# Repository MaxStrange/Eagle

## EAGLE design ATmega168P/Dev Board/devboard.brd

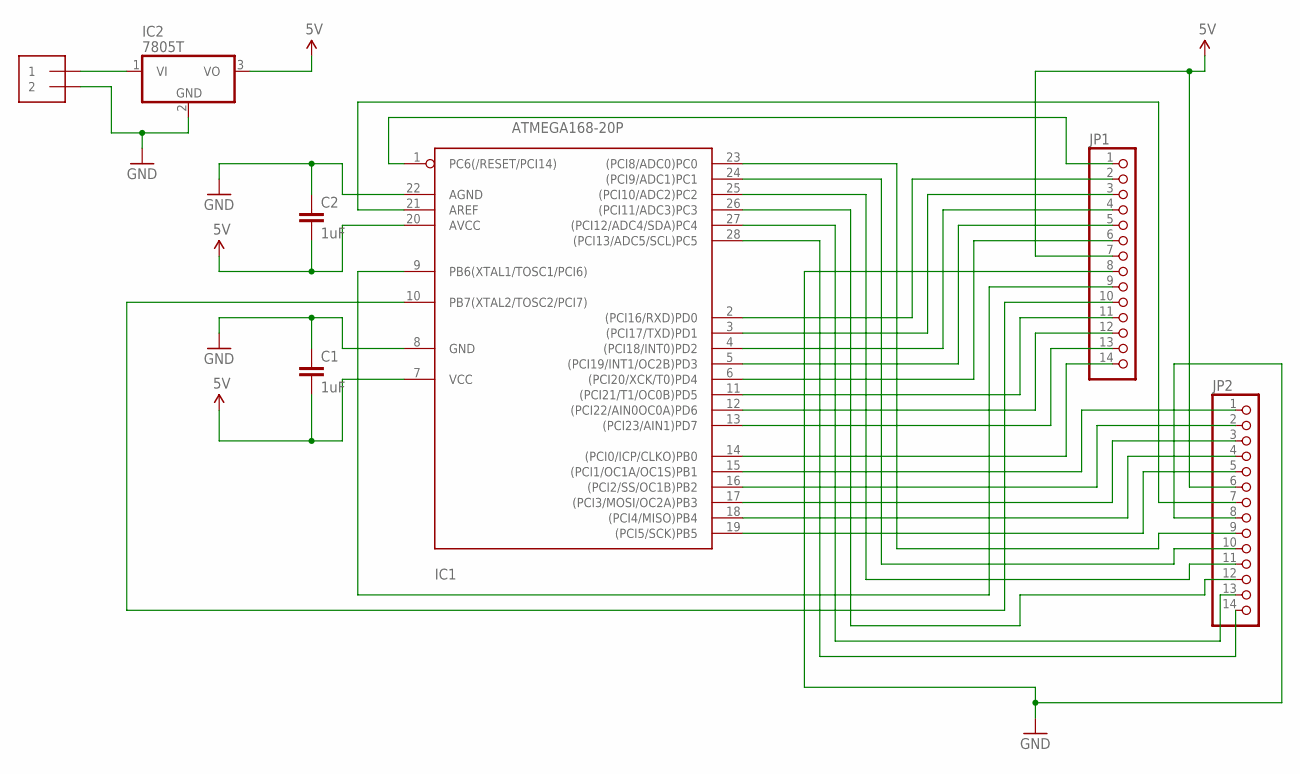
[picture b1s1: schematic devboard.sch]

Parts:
C1, C2: 1uF; CAP-PTH-SMALL
IC1: ATMEGA168-20P; DIL28-3
IC2: 7805T; TO220H
JP1, JP2: PINHD-1X14; 1X14
POWER_IN: 1X2-3.5MM

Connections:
GND: C1.1, C2.1, IC1.8 (GND), IC1.22 (AGND), IC2.2 (GND), JP1.8, JP2.8, POWER_IN.2
MISO: IC1.18 ((PCI4/MISO)PB4), JP2.4
MOSI: IC1.17 ((PCI3/MOSI/OC2A)PB3), JP2.3
unnamed: IC1.1 (PC6(/RESET/PCI14)), JP1.1
PIN2: IC1.2 ((PCI16/RXD)PD0), JP1.2
PIN3: IC1.3 ((PCI17/TXD)PD1), JP1.3
PIN4: IC1.4 ((PCI18/INT0)PD2), JP1.4
PIN5: IC1.5 ((PCI19/INT1/OC2B)PD3), JP1.5
PIN6: IC1.6 ((PCI20/XCK/T0)PD4), JP1.6
PIN9: IC1.9 (PB6(XTAL1/TOSC1/PCI6)), JP1.9
PIN10: IC1.10 (PB7(XTAL2/TOSC2/PCI7)), JP1.10
PIN11: IC1.11 ((PCI21/T1/OC0B)PD5), JP1.11
PIN12: IC1.12 ((PCI22/AIN0OC0A)PD6), JP1.12
PIN13: IC1.13 ((PCI23/AIN1)PD7), JP1.13
PIN14: IC1.14 ((PCI0/ICP/CLKO)PB0), JP1.14
PIN15: IC1.15 ((PCI1/OC1A/OC1S)PB1), JP2.1
PIN16: IC1.16 ((PCI2/SS/OC1B)PB2), JP2.2
PIN21: IC1.21 (AREF), JP2.7
PIN23: IC1.23 ((PCI8/ADC0)PC0), JP2.9
PIN24: IC1.24 ((PCI9/ADC1)PC1), JP2.10
PIN25: IC1.25 ((PCI10/ADC2)PC2), JP2.11
PIN26: IC1.26 ((PCI11/ADC3)PC3), JP2.12
PIN27: IC1.27 ((PCI12/ADC4/SDA)PC4), JP2.13
PIN28: IC1.28 ((PCI13/ADC5/SCL)PC5), JP2.14
SCK: IC1.19 ((PCI5/SCK)PB5), JP2.5
VCC: C1.2, C2.2, IC1.7 (VCC), IC1.20 (AVCC), IC2.3 (VO), JP1.7, JP2.6
VIN: IC2.1 (VI), POWER_IN.1

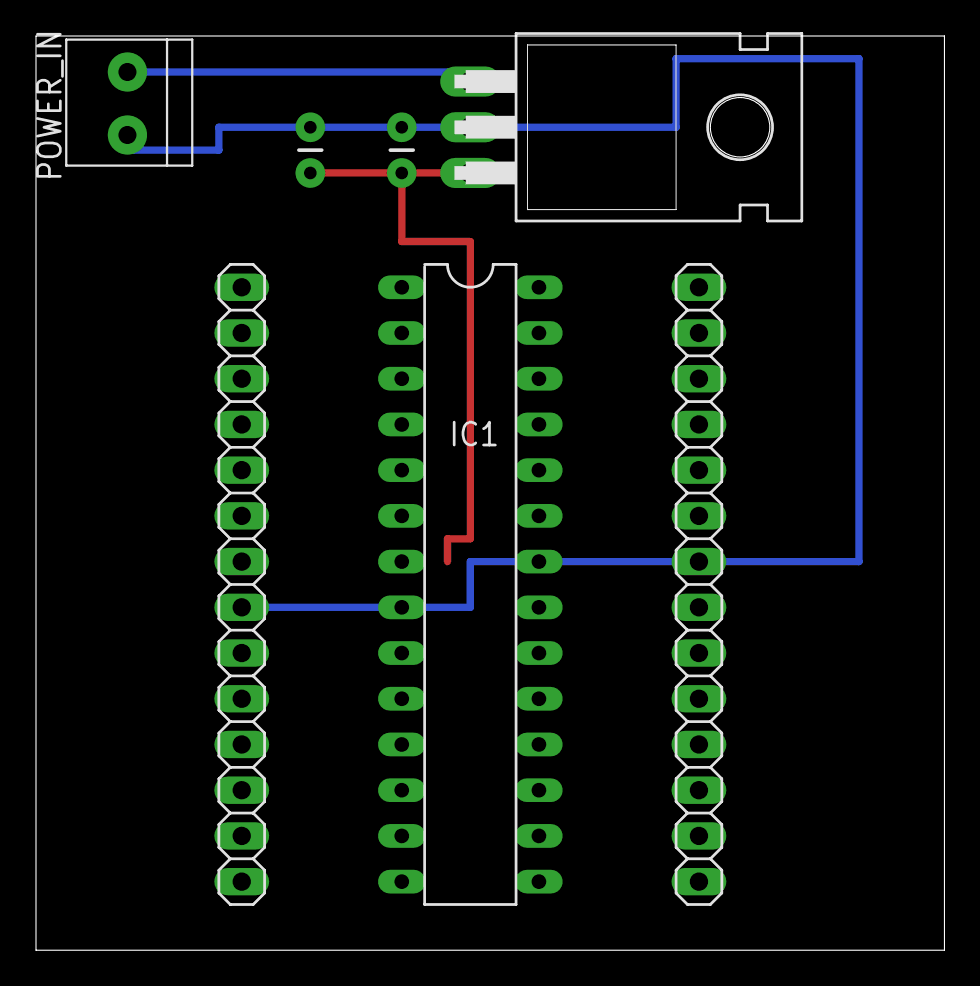
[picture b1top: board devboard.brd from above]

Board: 2 copper layers, 50.5 x 50.8 mm, 7 parts (0 on the bottom side), 27 nets.

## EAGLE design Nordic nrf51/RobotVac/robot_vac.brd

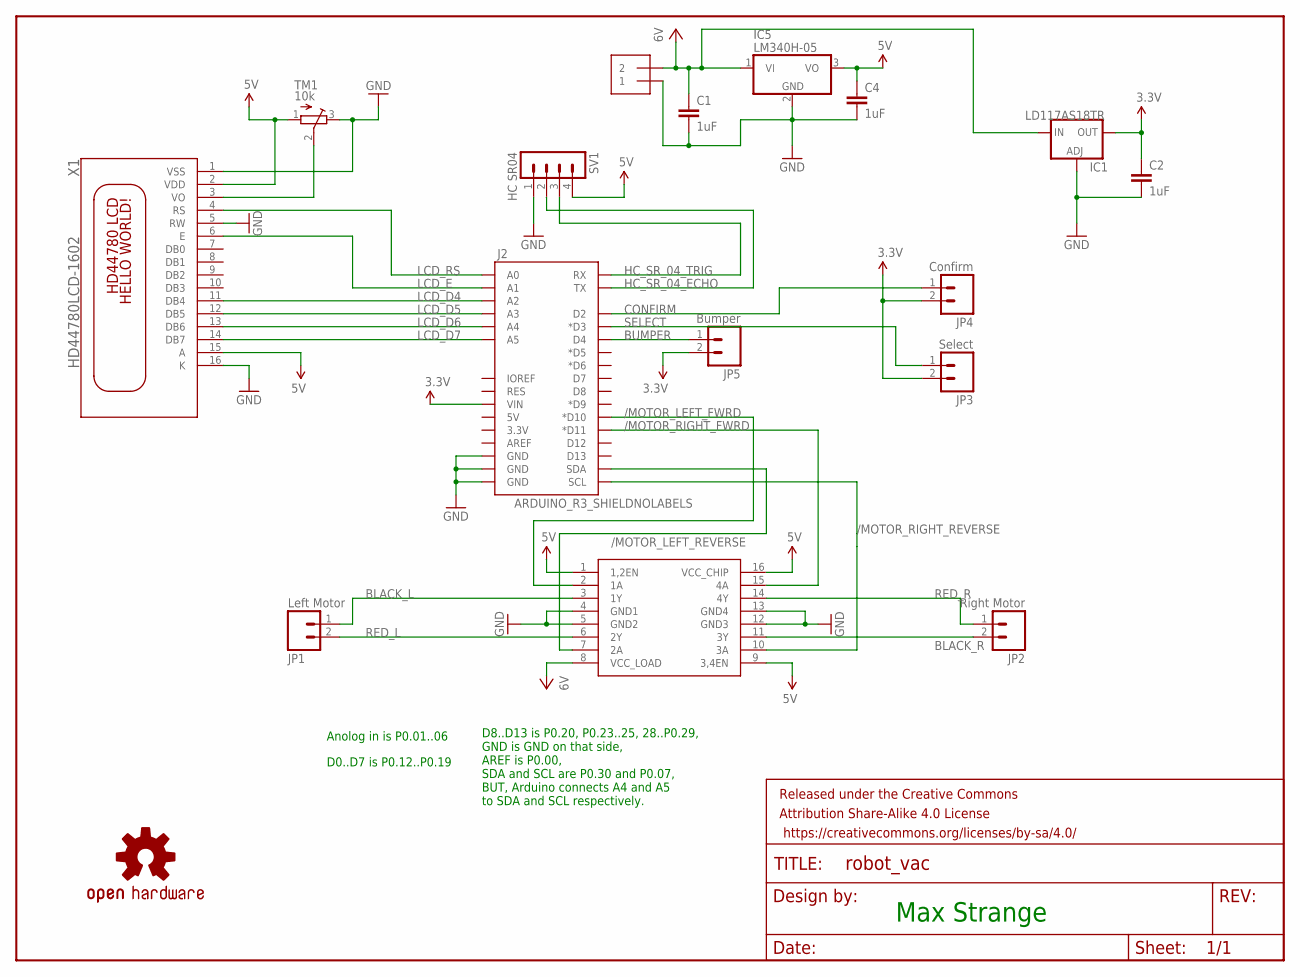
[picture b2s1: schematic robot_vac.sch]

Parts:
C1, C2, C4: 1uF; CAP-PTH-SMALL
FRAME1: FRAME-LETTERNO_PACKAGE; DUMMY
H_BRIDGE: SN75441_H_BRIDGE; DIL16
IC1: LD117AS18TR; SOT223
IC5: LM340H-05; TO220H
J1: 1X2-3.5MM
J2: ARDUINO_R3_SHIELDNOLABELS; UNO_R3_SHIELD_NOLABELS
JP1: Left Motor; 1X02_LOCK
JP2: Right Motor; 1X02_LOCK
JP3: Select; 1X02_LOCK
JP4: Confirm; 1X02_LOCK
JP5: Bumper; 1X02_LOCK
LOGO1: OSHW-LOGOL; OSHW-LOGO-L
SV1: HC SR04; MA04-1
TM1: 10k; TRIM-3386
X1: HD44780LCD-1602; LCD1602

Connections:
3.3V: C2.1, IC1.4 (OUT), J2.VIN, JP3.2, JP4.2, JP5.2
5V: C4.1, H_BRIDGE.1 (1,2EN), H_BRIDGE.9 (3,4EN), H_BRIDGE.16 (VCC_CHIP), IC5.3 (VO), SV1.4, TM1.1 (A), X1.2 (VDD), X1.15 (A)
/MOTOR_LEFT_FWRD: H_BRIDGE.2 (1A), J2.D10 (*D10)
/MOTOR_LEFT_REVERSE: H_BRIDGE.7 (2A), J2.SDA
/MOTOR_RIGHT_FWRD: H_BRIDGE.15 (4A), J2.D11 (*D11)
/MOTOR_RIGHT_REVERSE: H_BRIDGE.10 (3A), J2.SCL
BLACK_L: H_BRIDGE.3 (1Y), JP1.1
BLACK_R: H_BRIDGE.11 (3Y), JP2.2
BUMPER: J2.D4, JP5.1
CONFIRM: J2.D2, JP4.1
GND: C1.2, C2.2, C4.2, H_BRIDGE.4 (GND1), H_BRIDGE.5 (GND2), H_BRIDGE.12 (GND3), H_BRIDGE.13 (GND4), IC1.1 (ADJ), IC5.2 (GND), J1.1, J2.GND@0 (GND), J2.GND@1 (GND), J2.GND@2 (GND), SV1.1, TM1.3 (E), X1.1 (VSS), X1.5 (RW), X1.16 (K)
HC_SR_04_ECHO: J2.TX, SV1.2
HC_SR_04_TRIG: J2.RX, SV1.3
LCD_D4: J2.A2, X1.11 (DB4)
LCD_D5: J2.A3, X1.12 (DB5)
LCD_D6: J2.A4, X1.13 (DB6)
LCD_D7: J2.A5, X1.14 (DB7)
LCD_E: J2.A1, X1.6 (E)
LCD_RS: J2.A0, X1.4 (RS)
unnamed: TM1.2 (S), X1.3 (VO)
RED_L: H_BRIDGE.6 (2Y), JP1.2
RED_R: H_BRIDGE.14 (4Y), JP2.1
SELECT: J2.D3 (*D3), JP3.1
VCC: C1.1, H_BRIDGE.8 (VCC_LOAD), IC1.3 (IN), IC5.1 (VI), J1.2

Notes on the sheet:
Anolog in is P0.01..06
D0..D7 is P0.12..P0.19
D8..D13 is P0.20, P0.23..25, 28..P0.29, GND is GND on that side, AREF is P0.00, SDA and SCL are P0.30 and P0.07, BUT, Arduino connects A4 and A5 to SDA and SCL respectively.
Max Strange

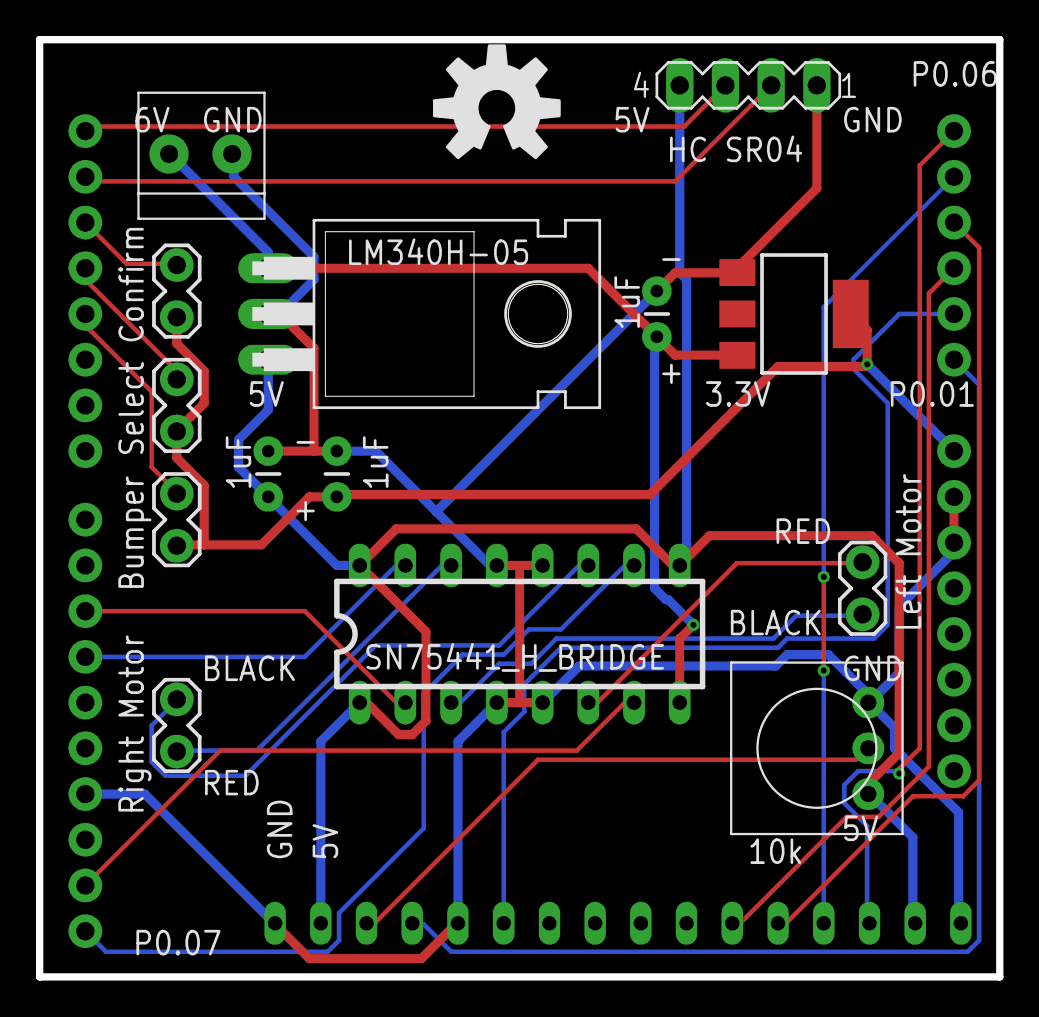
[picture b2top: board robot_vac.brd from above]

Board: 2 copper layers, 53.3 x 52.1 mm, 18 parts (0 on the bottom side), 24 nets.

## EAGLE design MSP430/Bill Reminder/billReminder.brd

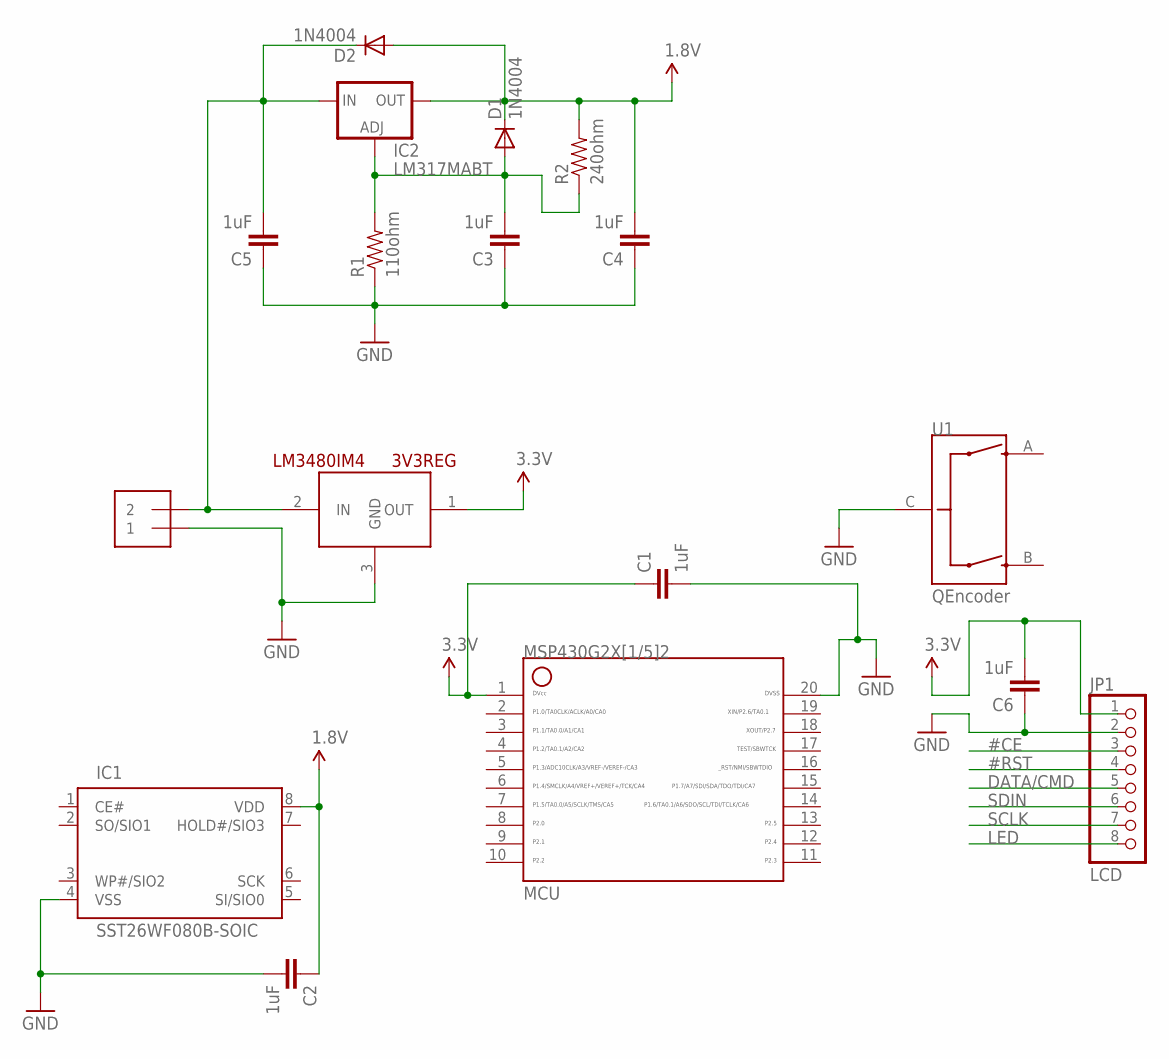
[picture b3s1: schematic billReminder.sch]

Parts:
3V3REG: LM3480IM4; SOT23-3
C1, C2, C3, C4, C5, C6: 1uF; CAP-PTH-SMALL
D1, D2: 1N4004; DO41-10
IC1: SST26WF080B-SOIC; SOIC08
IC2: LM317MABT; TO220L1
J1: 1X2-3.5MM
JP1: LCD; 1X08-CLEANBIG
MCU: G2X[1/5]2---N20; DIL20
R1: 110ohm; AXIAL-0.5
R2: 240ohm; AXIAL-0.5
U1: QEncoder; ENCODER-16MM-QUAD

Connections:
1.8V: C2.1, C4.2, D1.C, D2.A, IC1.8 (VDD), IC2.2 (OUT), R2.P$2 (2)
3.3V: 3V3REG.1 (OUT), C1.1, C6.2, JP1.1, MCU.1 (1_DVCC)
#CE: JP1.3
#RST: JP1.4
DATA/CMD: JP1.5
GND: 3V3REG.3 (GND), C1.2, C2.2, C3.1, C4.1, C5.1, C6.1, IC1.4 (VSS), J1.1, JP1.2, MCU.20 (20_DVSS), R1.P$1 (1), U1.C
LED: JP1.8
unnamed: 3V3REG.2 (IN), C5.2, D2.C, IC2.3 (IN), J1.2
unnamed: C3.2, D1.A, IC2.1 (ADJ), R1.P$2 (2), R2.P$1 (1)
SCLK: JP1.7
SDIN: JP1.6
SI/SIO0: IC1.5 (SI/SIO0)

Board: 2 copper layers, 17 parts (0 on the bottom side), 5 nets, no tracks yet.

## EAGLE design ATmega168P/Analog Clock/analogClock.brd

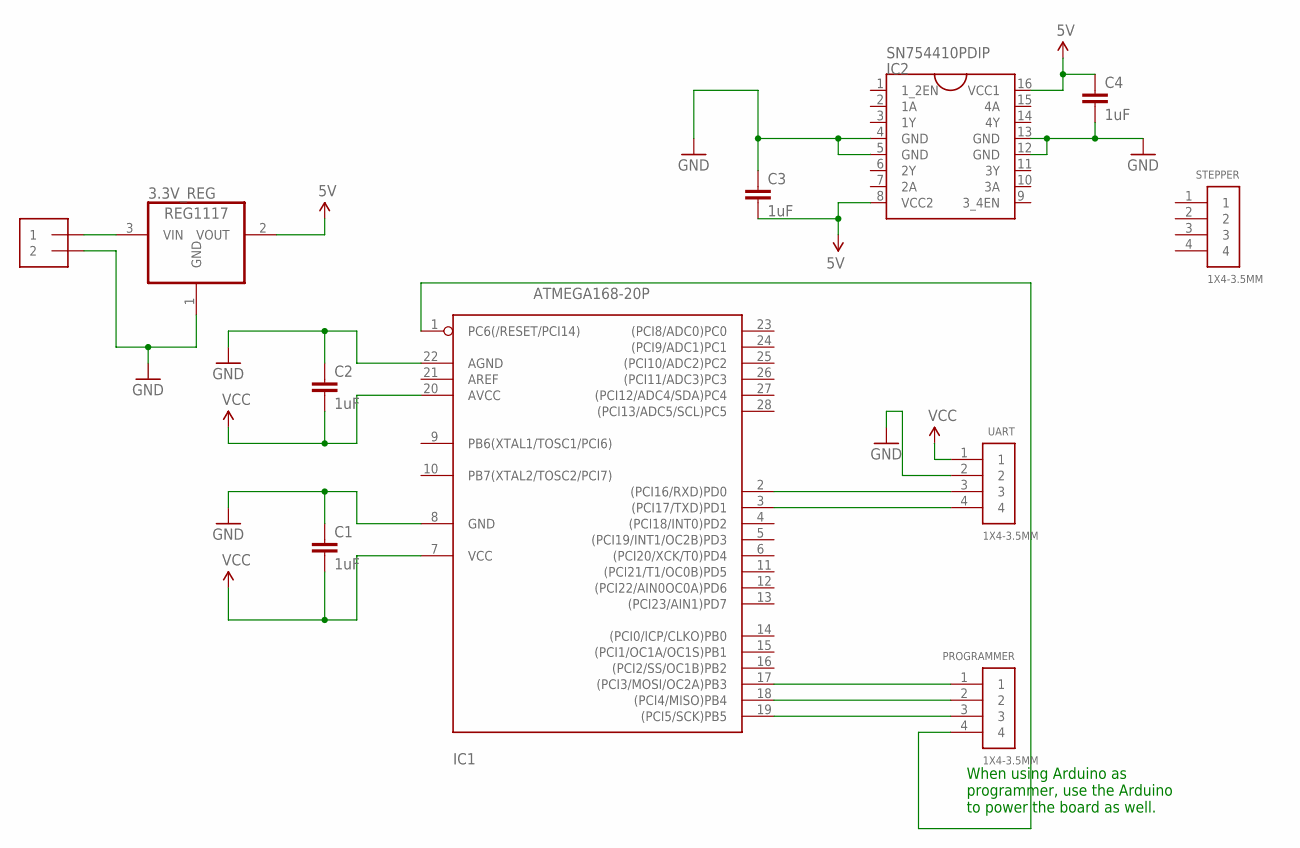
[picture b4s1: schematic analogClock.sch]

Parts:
3.3V_REG: REG1117; SOT223
C1, C2, C3, C4: 1uF; CAP-PTH-SMALL
IC1: ATMEGA168-20P; DIL28-3
IC2: SN754410PDIP; DIL16
POWER_IN: 1X2-3.5MM
PROGRAMMER: 1X4-3.5MM; 1X04-3.5MM
STEPPER: 1X4-3.5MM; 1X04-3.5MM
UART: 1X4-3.5MM; 1X04-3.5MM

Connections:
5V: 3.3V_REG.2 (VOUT), C3.2, C4.1, IC2.8 (VCC2), IC2.16 (VCC1)
GND: 3.3V_REG.1 (GND), C1.1, C2.1, C3.1, C4.2, IC1.8 (GND), IC1.22 (AGND), IC2.4 (GND), IC2.5 (GND), IC2.12 (GND), IC2.13 (GND), POWER_IN.2, UART.2
MISO: IC1.18 ((PCI4/MISO)PB4), PROGRAMMER.2
MOSI: IC1.17 ((PCI3/MOSI/OC2A)PB3), PROGRAMMER.1
unnamed: IC1.2 ((PCI16/RXD)PD0), UART.3
unnamed: IC1.3 ((PCI17/TXD)PD1), UART.4
RESET: IC1.1 (PC6(/RESET/PCI14)), PROGRAMMER.4
SCK: IC1.19 ((PCI5/SCK)PB5), PROGRAMMER.3
VCC: C1.2, C2.2, IC1.7 (VCC), IC1.20 (AVCC), UART.1
VIN: 3.3V_REG.3 (VIN), POWER_IN.1

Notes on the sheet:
When using Arduino as programmer, use the Arduino to power the board as well.

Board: 2 copper layers, 11 parts (0 on the bottom side), 10 nets, no tracks yet.

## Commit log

2016-01-25 :lollipop: Added .gitattributes & .gitignore files
2016-01-27 Update 1/26/16

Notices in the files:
parts and their libraries:
SparkFun-Capacitors: Licensing: Creative Commons ShareAlike 4.0 International - https://creativecommons.org/licenses/by-sa/4.0
SparkFun-Aesthetics: Released under the Creative Commons Attribution Share-Alike 4.0 License
SparkFun-Aesthetics: https://creativecommons.org/licenses/by-sa/4.0
